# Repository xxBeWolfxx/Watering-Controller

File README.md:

# Watering-Controller
Project created as a University's exam. It is based on Arduino Nano which controls two water pumps by relays.
## Watering Controller v1.0.0

**Description**:

It is a basic project which has got keypad (microswitches) and LCD to present a menu of aplication. Arduino checks values from humidity sensors and compares them to thresholds, which are saved in EEPROM. If the sensors's values are lower than thresholds's values, pumps start working. Arduino sets logical 0 or 1 on pumps's pins.

**PCB**:
PCB was created in KiCad (soon on GitHub). 

## Watering Controller v2.0.0

**Description**:

> Still in progress

*New version of my project*. I replaced a few components and added OLED(ssd1306) display and encoder. New  design has a RTC (DS1307) which improves a pump's working.

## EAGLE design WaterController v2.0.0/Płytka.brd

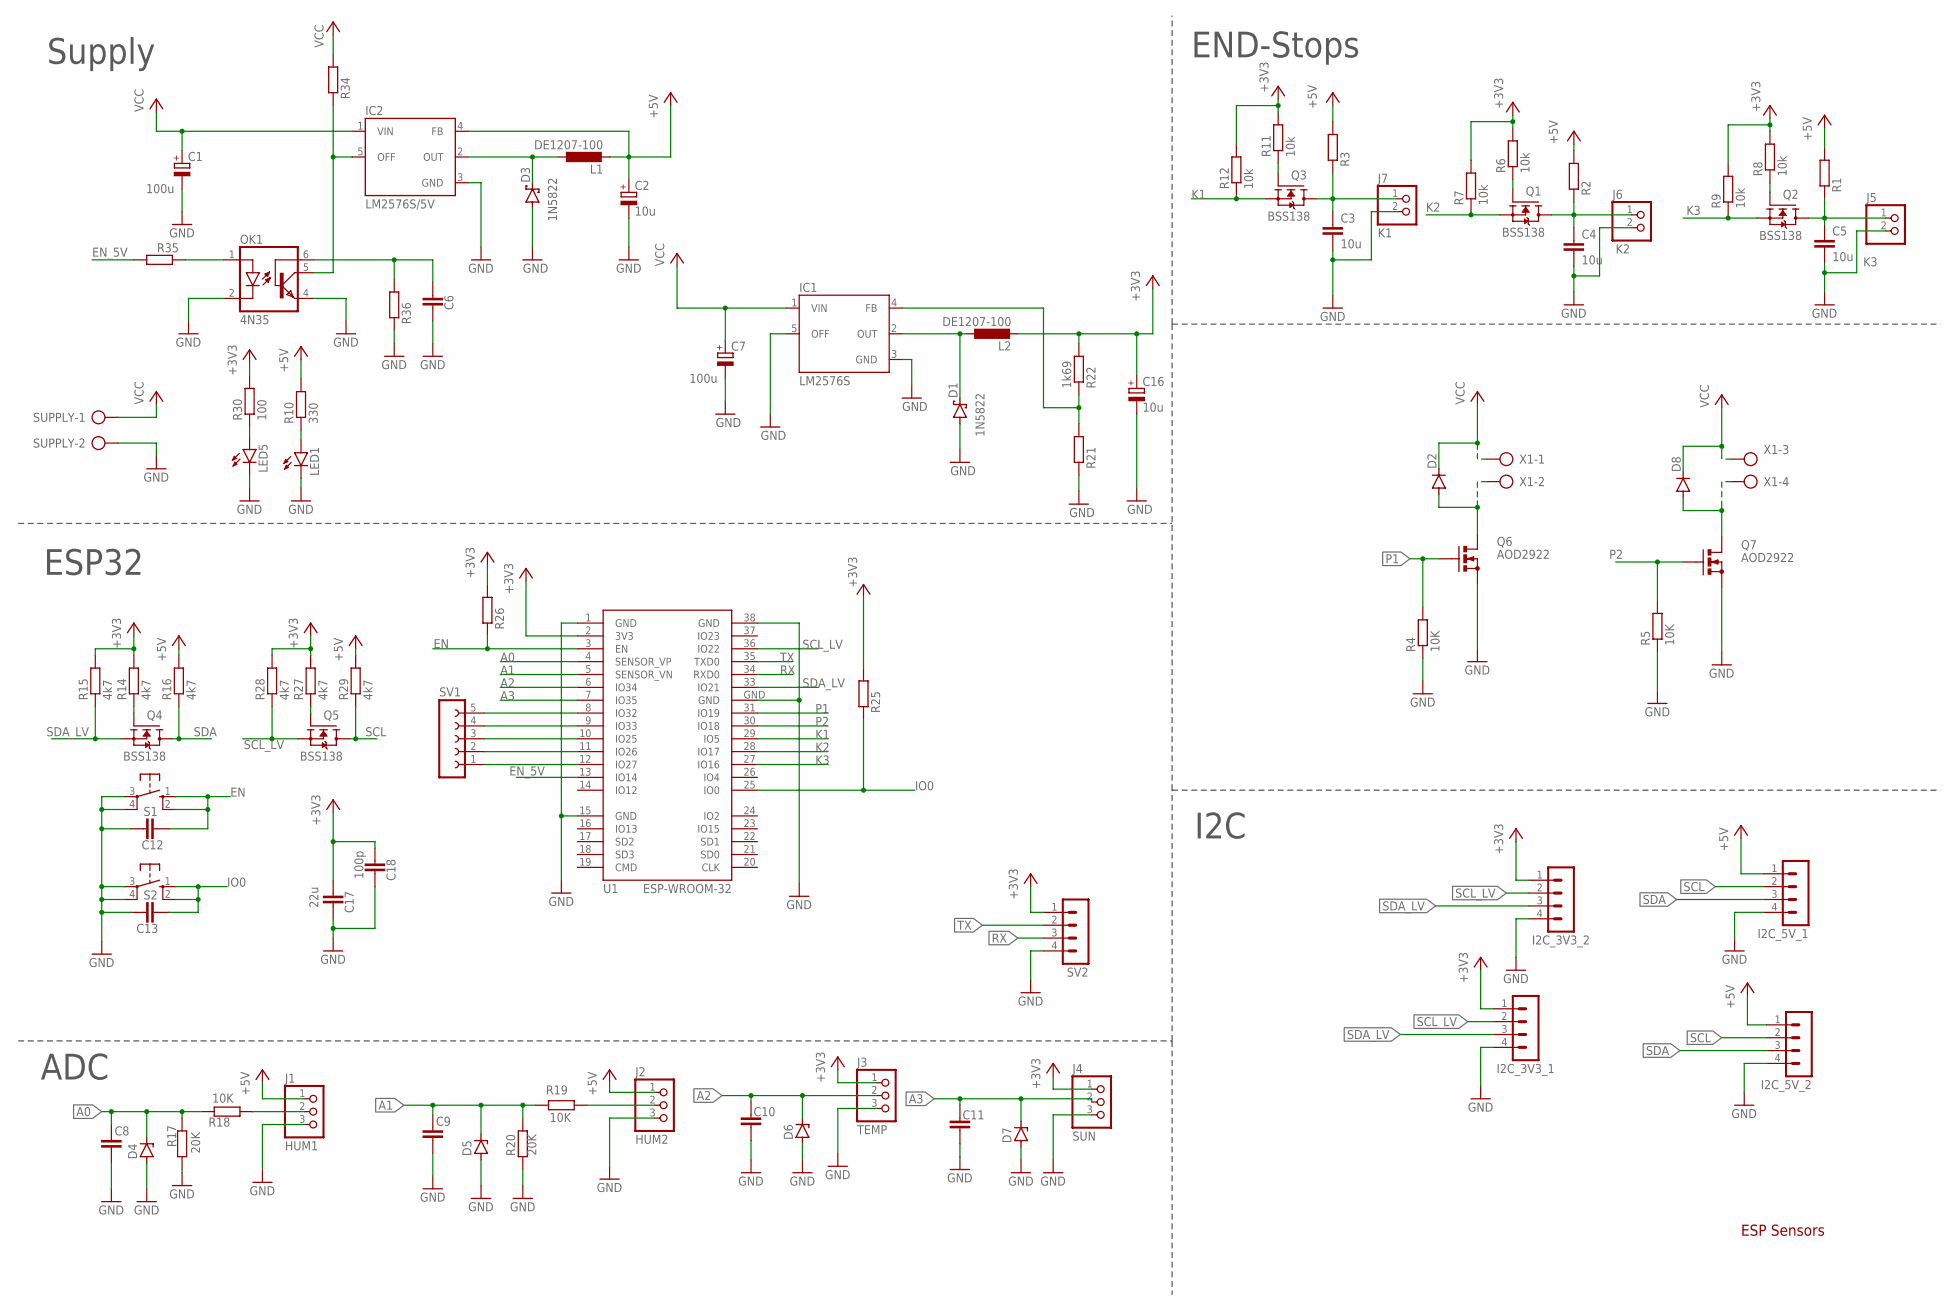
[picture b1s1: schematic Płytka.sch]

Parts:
C1, C7: 100u; E2,5-6
C2, C16: 10u; E3,5-8
C3, C4, C5: 10u; C0805K
C6, C8, C9, C10, C11, C12, C13: C-EUC0805K; C0805K
C17: 22u; C0805K
C18: 100p; C0805K
D1, D3: 1N5822; C4111-15
D2, D8: DIODE-DO214AC; DO214AC
D4, D5, D6, D7: ZENER-DIODESOD80C; SOD80C
I2C_3V3_1, I2C_3V3_2, I2C_5V_1, I2C_5V_2: MA04-1
IC1: LM2576S; TO263-5
IC2: LM2576S/5V; TO220-5
J1: HUM1; W_TYPE_2MM_3_N
J2: HUM2; W_TYPE_2MM_3_N
J3: TEMP; W_TYPE_2MM_3_N
J4: SUN; W_TYPE_2MM_3_N
J5: K3; W_TYPE_2MM_2_N
J6: K2; W_TYPE_2MM_2_N
J7: K1; W_TYPE_2MM_2_N
L1, L2: DE1207-100; DE1207
LED1, LED5: LEDSML0805; SML0805
OK1: 4N35; DIL06
Q1, Q2, Q3, Q4, Q5: BSS138; SOT23
Q6, Q7: AOD2922; TO252AA
R1, R2, R3, R21, R25, R26, R34, R35, R36: R-EU_R0805; R0805
R4, R5, R18, R19: 10K; R0805
R6, R7, R8, R9, R11, R12: 10k; R0805
R10: 330; R0805
R14, R15, R16, R27, R28, R29: 4k7; R0805
R17, R20: 20K; R0805
R22: 1k69; R0805
R30: 100; R0805
S1, S2: 10-XX; B3F-10XX
SUPPLY: AK500/2-H
SV1: FE05-1
SV2: MA04-1
U1: ESP-WROOM-32
X1: + P2; AK500/4

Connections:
+3V3: C16.+, C17.2, C18.2, I2C_3V3_1.1, I2C_3V3_2.1, J3.1, J4.1, L2.2, R6.2, R7.2, R8.2, R9.2, R11.2, R12.2, R14.2, R15.2, R22.2, R25.2, R26.2, R27.2, R28.2, R30.2, SV2.1, U1.2 (3V3)
+5V: C2.+, I2C_5V_1.1, I2C_5V_2.1, IC2.4 (FB), J1.1, J2.1, L1.2, R1.2, R2.2, R3.2, R10.2, R16.2, R29.2
A0: C8.1, D4.C, R17.2, R18.2, U1.4 (SENSOR_VP)
A1: C9.1, D5.C, R19.2, R20.1, U1.5 (SENSOR_VN)
A2: C10.1, D6.C, J3.2, U1.6 (IO34)
A3: C11.1, D7.C, J4.2, U1.7 (IO35)
EN: C12.2, R26.1, S1.1 (S), S1.2 (S1), U1.3 (EN)
EN_5V: R35.2, U1.13 (IO14)
GND: C1.-, C2.-, C3.2, C4.2, C5.2, C6.1, C7.-, C8.2, C9.2, C10.2, C11.2, C12.1, C13.1, C16.-, C17.1, C18.1, D1.A, D3.A, D4.A, D5.A, D6.A, D7.A, I2C_3V3_1.4, I2C_3V3_2.4, I2C_5V_1.4, I2C_5V_2.4, IC1.3 (GND), IC1.5 (OFF), IC2.3 (GND), J1.3, J2.3, J3.3, J4.3, J5.2, J6.2, J7.2, LED1.C, LED5.C, OK1.2 (C), OK1.4 (EMI), Q6.2 (S), Q7.2 (S), R4.1, R5.1, R17.1, R20.2, R21.1, R36.1, S1.3, S1.4 (P1), S2.3, S2.4 (P1), SUPPLY.2, SV2.4, U1.1 (GND), U1.15 (GND), U1.38 (GND), U1.GND
IO0: C13.2, R25.1, S2.1 (S), S2.2 (S1), U1.25 (IO0)
K1: Q3.2 (S), R12.1, U1.29 (IO5)
K2: Q1.2 (S), R7.1, U1.28 (IO17)
K3: Q2.2 (S), R9.1, U1.27 (IO16)
unnamed: C5.1, J5.1, Q2.3 (D), R1.1
unnamed: C4.1, J6.1, Q1.3 (D), R2.1
unnamed: LED1.A, R10.1
unnamed: Q4.1 (G), R14.1
unnamed: C3.1, J7.1, Q3.3 (D), R3.1
unnamed: D2.A, Q6.3 (D), X1.2
unnamed: D8.A, Q7.3 (D), X1.4
unnamed: Q5.1 (G), R27.1
unnamed: J1.2, R18.1
unnamed: SV1.5, U1.8 (IO32)
unnamed: Q1.1 (G), R6.1
unnamed: SV1.4, U1.9 (IO33)
unnamed: Q2.1 (G), R8.1
unnamed: SV1.3, U1.10 (IO25)
unnamed: Q3.1 (G), R11.1
unnamed: SV1.2, U1.11 (IO26)
unnamed: J2.2, R19.1
unnamed: D3.C, IC2.2 (OUT), L1.1
unnamed: D1.C, IC1.2 (OUT), L2.1
unnamed: SV1.1, U1.12 (IO27)
unnamed: LED5.A, R30.1
unnamed: IC2.5 (OFF), OK1.5 (COL), R34.1
unnamed: OK1.1 (A), R35.1
unnamed: C6.2, OK1.6 (BAS), R36.2
unnamed: IC1.4 (FB), R21.2, R22.1
P1: Q6.1 (G), R4.2, U1.31 (IO19)
P2: Q7.1 (G), R5.2, U1.30 (IO18)
RX: SV2.3, U1.34 (RXD0)
SCL: I2C_5V_1.2, I2C_5V_2.2, Q5.3 (D), R29.1
SCL_LV: I2C_3V3_1.2, I2C_3V3_2.2, Q5.2 (S), R28.1, U1.36 (IO22)
SDA: I2C_5V_1.3, I2C_5V_2.3, Q4.3 (D), R16.1
SDA_LV: I2C_3V3_1.3, I2C_3V3_2.3, Q4.2 (S), R15.1, U1.33 (IO21)
TX: SV2.2, U1.35 (TXD0)
VCC: C1.+, C7.+, D2.C, D8.C, IC1.1 (VIN), IC2.1 (VIN), R34.2, SUPPLY.1, X1.1, X1.3

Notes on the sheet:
Supply
ESP32
ADC
I2C
END-Stops
ESP Sensors

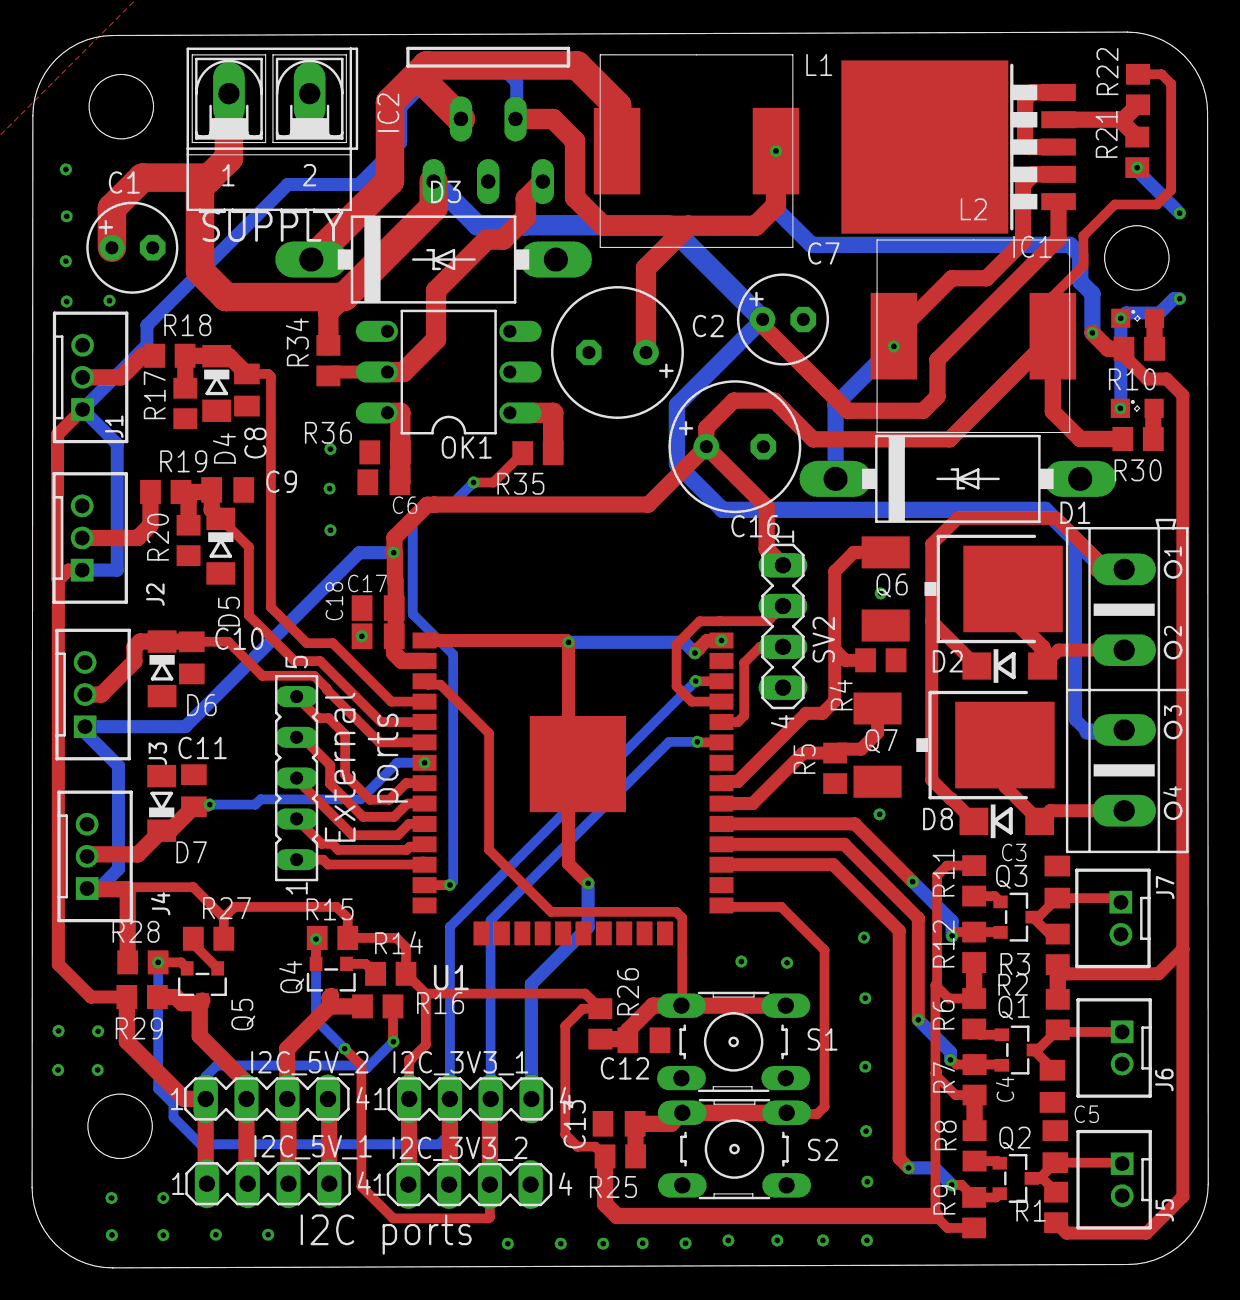
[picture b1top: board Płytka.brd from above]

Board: 2 copper layers, 73.3 x 77.0 mm, 86 parts (0 on the bottom side), 47 nets.

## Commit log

2019-11-12 Initialize project
2019-11-14 Add function to controll LCD
2019-11-14 Add values to analogRead
2019-11-14 Add a mapping swtich to values
2020-01-06 Add menu, reading sensors etc.
2020-01-06 Add preparation for pinMode
2020-01-08 Add commentary to code
2020-01-10 Assembly the Arduino to pcb board
2020-01-16 Change value of sensors
2020-01-19 End project with v1.0.0
2020-01-19 Improve SensoreRead function, adding a average of readings
2020-01-19 add commentaries
2020-04-29 Add Eagle project of PCB
2020-04-29 no message
2020-04-29 Add .gitignore
2020-04-29 Add Eagle project
2020-05-01 Change old functions
2020-05-24 Add new lines of code
2020-06-08 End schematic in eagle
2020-06-08 Add PCB
2020-06-13 Add new items in PCB
2020-06-15 Preparing OLED display
2020-06-15 Change reset pin of OLED
2020-06-19 Add new sensor
2020-06-26 Change name of sensors
2020-06-26 Create a readme
2020-07-14 Add sth
2021-08-24 Add new board from another project
2021-08-25 Create new board
2021-09-12 improve board schematic
2021-09-14 correct mistakes in board
2021-09-15 Create platformio project
2021-09-16 Add new class
2021-09-18 Add new methods in PIDcontroller
2021-09-24 Add new methods to PID controller
2021-09-27 Add handler for DS18B20
2021-10-05 Add new variables
2021-11-22 Add deconstruct
2022-11-10 new components
2022-11-15 Add Daemon for websocket in RPi
2022-11-18 add gitignore
2022-11-26 Create basic websocket service
2022-11-27 add reading data from config
2022-12-20 Split functions to class's method of websocket and boost
2022-12-30 add thread for websocket class
2023-01-09 Remade classes to async mode
2023-01-17 Update workflow
2023-01-18 Rename, add special thread for websocket, killing ptrs
2023-01-26 Add data receiving, sending confirmation
2023-01-29 Update Database for watering controller
2023-02-02 Add database for tests
2023-02-09 Update database
2023-02-11 Update rpi database
2023-02-12 Create dynamic methods for database
2023-02-17 Add unit tests
2023-02-20 Add unit libs to tests
2023-03-06 Add virtual class Record
2023-03-07 Add bridge to websocket
2023-03-13 Divided WebsocketService to two headers
2023-03-26 Add message validation
2023-03-27 Fix leak memory
2023-04-02 add checking esp in database
2023-04-03 cleaning switch case in Record.cpp
2023-04-08 Add Flower class and Measurement struct
2023-04-23 Add reading records of Flower
2023-04-26 add method to calculate avg
2023-04-28 Add update database function
2023-05-10 Database service done
2023-06-19 Add logger class
2023-07-23 Add closing for unfamiliar esp
2023-07-23 Fix segmentation fault if data is empty
2023-07-28 Add json validation
2023-07-30 validation messages with measurments
2023-08-21 Add update measurments to database
2023-11-14 rewrite classes
2023-11-14 Revert "rewrite classes"
    This reverts commit ab6437bf6bed25d2474dc62d9f2fb126a8e2b91d.
2023-11-14 make seprate classes for data and websocket

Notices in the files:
parts and their libraries:
esp32: Creative Commons Attribution-ShareAlike 4.0 International
